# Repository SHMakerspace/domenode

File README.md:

# domenode
A CAN bus controlled, WiFi enabled network of dome node LEDs with many features

# Features
* :heavy_check_mark: ESP32 microcontroller (WiFi, bluetooth)
  * Pads for both ESP32 standalone module and dev board variants
  * OTA wireless firmware updates
* :heavy_check_mark: SN65HVD230 CAN bus transceiver
* :heavy_check_mark: 2x RJ45 connectors for CAN in and passthrough
* :heavy_check_mark: 5x WS2812/NeoPixel for RGB lighting
* :heavy_check_mark: On-board buck regulator
* :heavy_check_mark: 2x push switches
* :heavy_check_mark: Power and GPIO LED
* :heavy_check_mark: many headers for sensors and attachments (I2C, GPIOs, power etc)
* :red_circle: A shield header for expansion boards (to be added)

# Sensors (all optional and do not need to be populated)
Optional features by means of populating those pads are:
* :question: Outer and inner facing LDRs for ambient/transmitted light sensing
* :question: 2x tactile push switches for on-board input
* :question: Heavier duty power RGB LED shield connector (exposes 24V and R,G,B GPIOs)
* :question: IR Tx/Rx and (hopefully!) a ghetto distance sensor
* :question: Speaker
* :question: Capacitive touch
* :question: Microphone - MAX4466 based breakout board connector (footprints could be added to board, alternative idea is I2S)

# Firmware notes
* CAN bus - http://www.barth-dev.de/can-driver-esp32/
* NeoPixels - https://www.instructables.com/id/ESP32-Bluetooth-Ambience-Light-Controller-With-WS2/
* Microphone -https://www.hackster.io/julianfschroeter/esp32-voice-streamer-52bd7e , https://github.com/MrBuddyCasino/ESP32_Alexa
* Speaker - http://www.xtronical.com/basics/audio/dacs-on-esp32/
* IR sensor - https://github.com/mdhiggins/ESP8266-HTTP-IR-Blaster
* I2C bus - https://randomnerdtutorials.com/esp32-with-bmp180-barometric-sensor/

# BoM and Components

## 1. Basic functionality and programming
* 1x ESP32 module
* 1x SOT-223 3v3 LDO regulator
* 2x 0603 10uF ceramic capacitors (decoupling)
* 2x 100uF tantalum capacitors (decoupling)
* 1x 4 pin ISP header
* 1x 2 pin SW0 flashing header
* 2x 0805 LED (power and blink)
* 2x 0603 resistors for LEDs (470 and 1k)
* 1x 0603 10k resistor EN (very much needed, R10)

## 2. NeoPixels
* 9x WS2812 LEDs
* 1x 0603 470 ohm resistor (R13)
* 9x 0603 100nF ceramic capacitors

## 3. External Power
* 1x MINI-360 buck regulator module (U1)
* 1x 1N5819 protection diode
* 1x 1210 10uF >24v capacitor (C1)
* 2x 0603 10uF ceramic capacitors (C2, C4 decoupling)
* 2x RJ45 connectors

## 4. CAN Bus
* 1x SN65HVD230DR transceiver IC (U6)
* 1x 2 pin CANTERM header
* 1x 0603 120 ohm resistor (R16)
* 1x 0603 10k resistor (R17)
* 1x 0603 100nF capacitor (C14, decoupling)

# Serial Programming
Order is:
Black, Green, White, Red 
(GND), (Rx), (Tx), (5V)

#Flashing Procedure
* 1. Determine COM port with command `mode`
* 2. Open terminal in esp32 python environment
* 3. esptool --chip esp32 -p COM<x> write_flash -z 0x1000 <firmware_bin>

Uploading files

ampy -p COM<x> put <file>

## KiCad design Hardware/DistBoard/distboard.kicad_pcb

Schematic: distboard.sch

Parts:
C1: 100uF; CP_EIA-3528-21_Kemet-B_Pad1.50x2.35mm_HandSolder
C2: 10uF; C_0603_1608Metric_Pad1.05x0.95mm_HandSolder
D1: 1N5819; D_DO-41_SOD81_P10.16mm_Horizontal
F1: Fuse; BladeFuse-Mini
J1: POWER_IN; Wago_734-162_1x02_P3.50mm_Horizontal
J2: FAN_HEADER; Molex_KK-6410-02_02x2.54mm_Straight
J4: CAN_1; RJ45_GENERIC
J5: CAN_PI; RJ45_GENERIC
J6: CAN_2; RJ45_GENERIC
J7: CAN_3; RJ45_GENERIC
J8: CAN_4; RJ45_GENERIC
MH1, MH2, MH3, MH4: MountingHole_Pad; MountingHole_3.2mm_M3_Pad_Via
U1: MINI-360
U2, U3, U4: double_usb; USB_A_Wuerth_61400826021_Horizontal_Stacked

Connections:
+5V: C1.1, C2.1, J2.1, U1.4, U2.1, U2.5, U3.1, U3.5, U4.1, U4.5; also elsewhere on the board
CANGND: C1.2, C2.2, J1.2, J2.2, J4.4, J4.5, J4.6, J4.SH, J5.4, J5.5, J5.6, J5.SH, J6.4, J6.5, J6.6, J6.SH, J7.4, J7.5, J7.6, J7.SH, J8.4, J8.5, J8.6, J8.SH, MH1.1, MH2.1, MH3.1, MH4.1, U1.2, U1.3, U2.4, U2.8, U2.9, U3.4, U3.8, U3.9, U4.4, U4.8, U4.9; also elsewhere on the board
CANH: J4.7, J5.7, J6.7, J7.7, J8.7
CANL: J4.8, J5.8, J6.8, J7.8, J8.8
CANV: D1.1 (K), J4.1, J4.2, J4.3, J5.1, J5.2, J5.3, J6.1, J6.2, J6.3, J7.1, J7.2, J7.3, J8.1, J8.2, J8.3, U1.1
unnamed: D1.2 (A), F1.2
unnamed: F1.1, J1.1

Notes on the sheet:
1: VCC 2: VCC 3: VCC 4: GND 5: GND 6: GND 7: CAN+ 8: CAN-

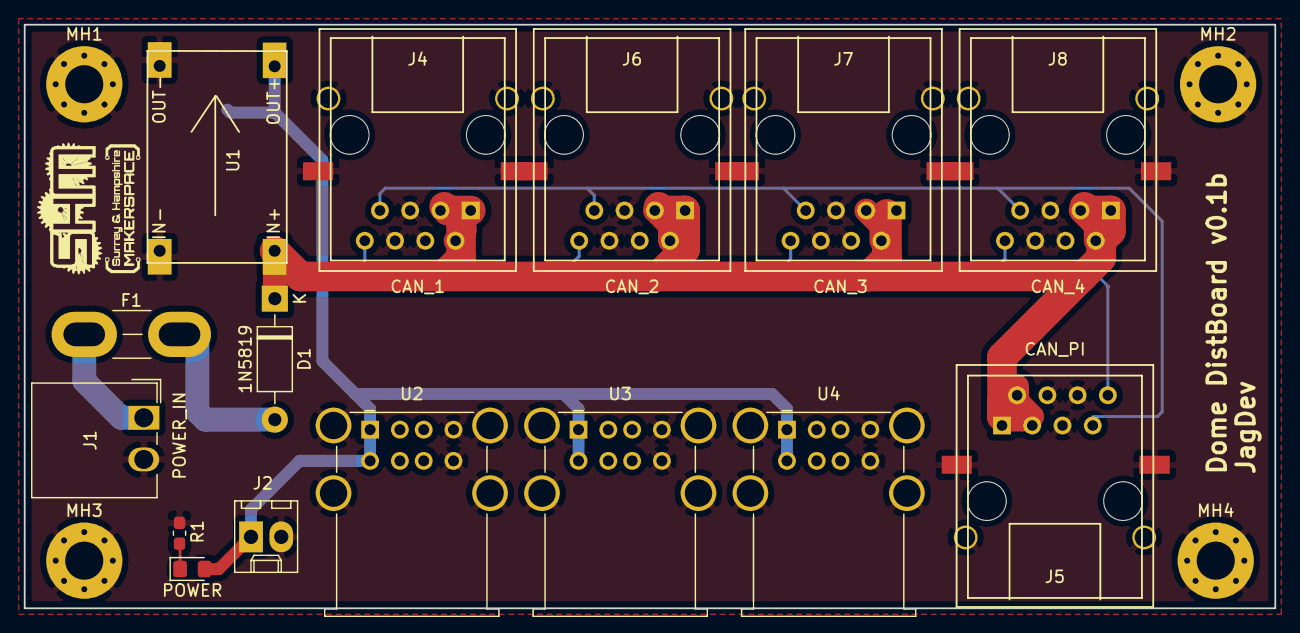
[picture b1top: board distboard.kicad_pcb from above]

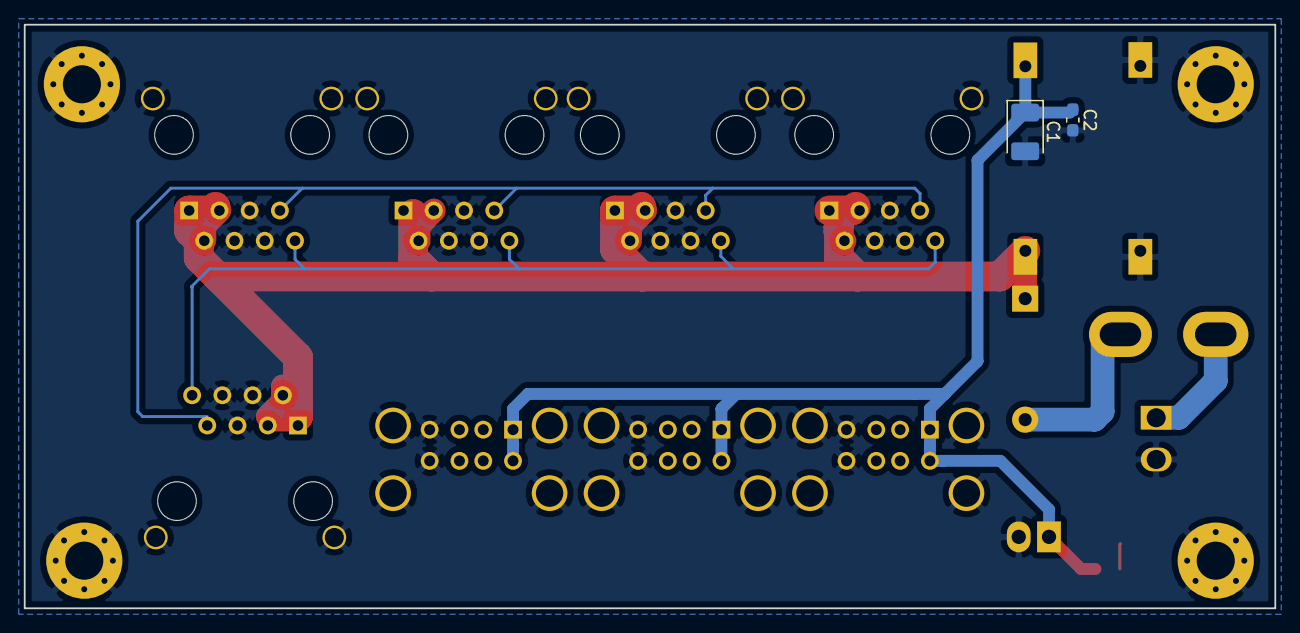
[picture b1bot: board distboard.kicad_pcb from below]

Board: 2 copper layers, 105.0 x 49.0 mm, 22 parts (2 on the bottom side), 8 nets.

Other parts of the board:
D2: POWER; LED_0805_2012Metric_Pad1.15x1.40mm_HandSolder
R1: 1K; R_0603_1608Metric_Pad1.05x0.95mm_HandSolder
shm_logo_small: shm_logo_small

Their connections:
+5V: D2.2; also elsewhere on the board
CANGND: R1.2; also elsewhere on the board
unnamed: D2.1, R1.1

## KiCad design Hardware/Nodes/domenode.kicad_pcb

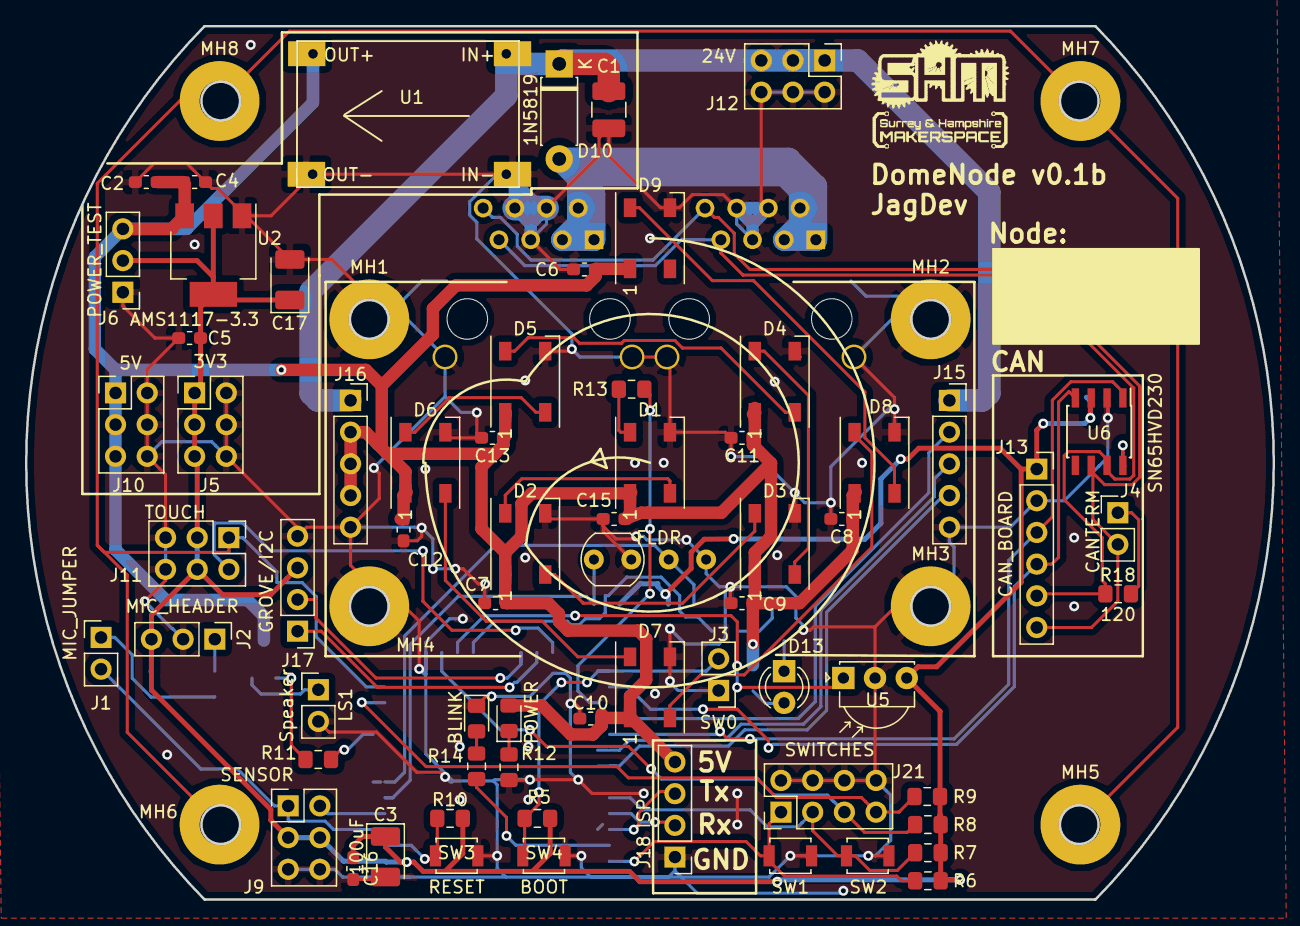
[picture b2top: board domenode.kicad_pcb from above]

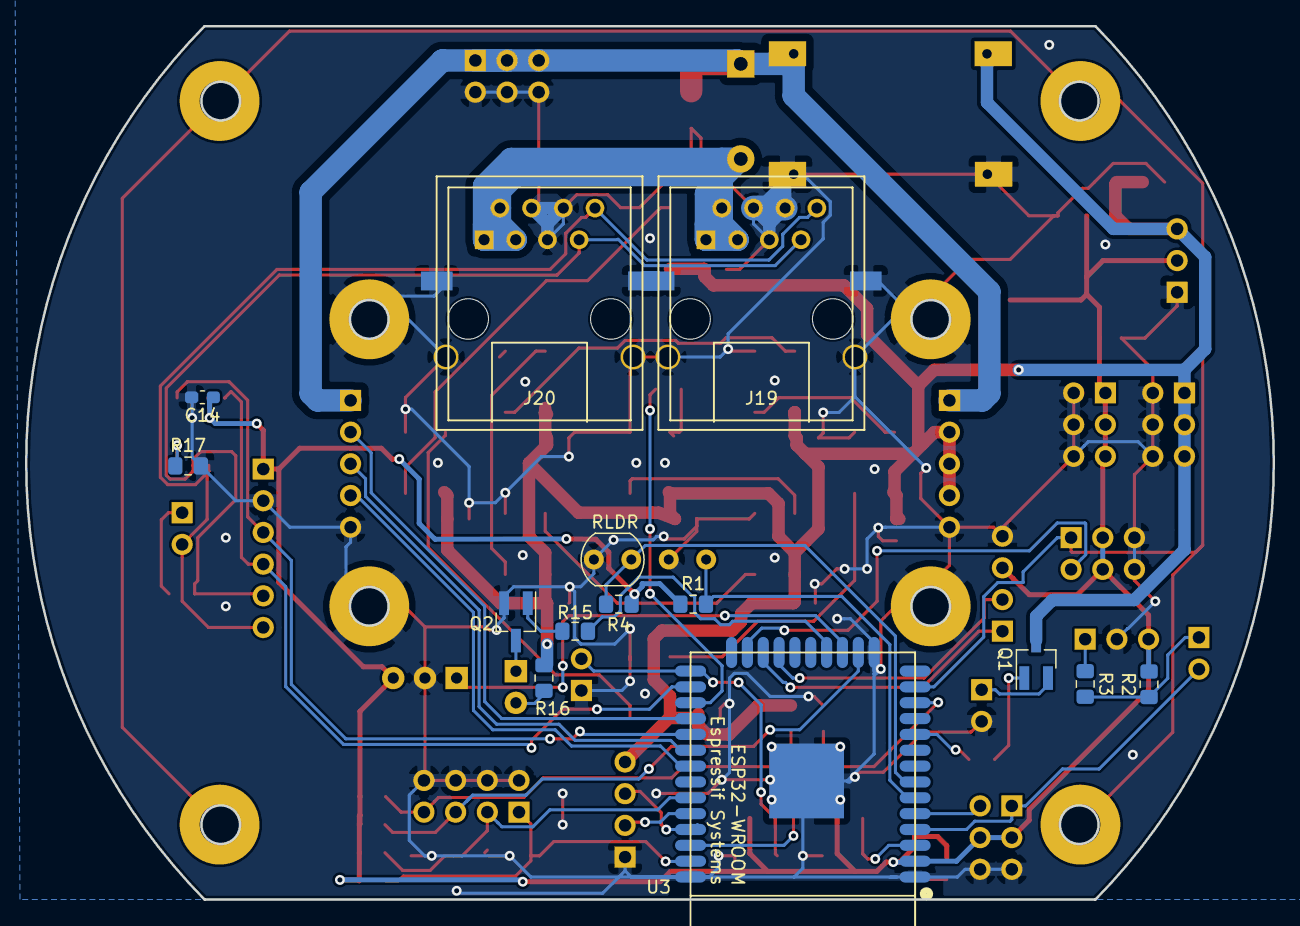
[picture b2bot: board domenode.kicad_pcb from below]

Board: 2 copper layers, 100.0 x 70.0 mm, 89 parts (14 on the bottom side), 53 nets.

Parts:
C1: 10uF; C_1210_3225Metric_Pad1.42x2.65mm_HandSolder
C2, C4, C5, C16: 10uF; C_0603_1608Metric_Pad1.05x0.95mm_HandSolder
C3, C17: 100uF; CP_EIA-3528-21_Kemet-B_Pad1.50x2.35mm_HandSolder
C6, C7, C8, C9, C10, C11, C12, C13, C14, C15: 100nF; C_0603_1608Metric_Pad1.05x0.95mm_HandSolder
D1, D2, D3, D4, D5, D6, D7, D8, D9: WS2812B; LED_WS2812B_PLCC4_5.0x5.0mm_P3.2mm
D10: 1N5819; D_DO-41_SOD81_P7.62mm_Horizontal
D11: POWER; LED_0805_2012Metric_Pad1.15x1.40mm_HandSolder
D12: BLINK; LED_0805_2012Metric_Pad1.15x1.40mm_HandSolder
D13: IRLED; LED_D3.0mm_IRBlack
J1: MIC_JUMPER; PinHeader_1x02_P2.54mm_Vertical
J2: MIC_HEADER; PinHeader_1x03_P2.54mm_Vertical
J3: SW0; PinHeader_1x02_P2.54mm_Vertical
J4: CANTERM; PinHeader_1x02_P2.54mm_Vertical
J5: 3V3; PinHeader_2x03_P2.54mm_Vertical
J6: POWER_TEST; PinHeader_1x03_P2.54mm_Vertical
J9: SENSOR; PinHeader_2x03_P2.54mm_Vertical
J10: 5V; PinHeader_2x03_P2.54mm_Vertical
J11: TOUCH; PinHeader_2x03_P2.54mm_Vertical
J12: 24V; PinHeader_2x03_P2.54mm_Vertical
J13: CAN_BOARD; PinSocket_1x06_P2.54mm_Vertical
J15, J16: RGB_SHIELD; PinSocket_1x05_P2.54mm_Vertical
J17: GROVE/I2C; PinHeader_1x04_P2.54mm_Vertical
J18: ISP; PinHeader_1x04_P2.54mm_Vertical
J19: CAN_IN; RJ45_GENERIC
J20: CAN_OUT; RJ45_GENERIC
J21: SWITCHES; PinHeader_2x04_P2.54mm_Vertical
LDR1: FLDR; Resistor_LDR_5x4.1_RM3
LDR2: RLDR; Resistor_LDR_5x4.1_RM3
LS1: Speaker; PinHeader_1x02_P2.54mm_Vertical
MH1, MH2, MH3, MH4: GND; MountingHole_3.2mm_M3_Pad
MH5, MH6, MH7, MH8: TOUCH5; MountingHole_3.2mm_M3_Pad
Q1: MMBT918 (2N706 equiv); SOT-23_Handsoldering
Q2: MMBT2222A (2N2222 equiv); SOT-23_Handsoldering
R1, R4: 100k; R_0805_2012Metric_Pad1.15x1.40mm_HandSolder
R2: 4K; R_0805_2012Metric_Pad1.15x1.40mm_HandSolder
R3: 5K; R_0805_2012Metric_Pad1.15x1.40mm_HandSolder
R5, R6, R7, R8, R9, R10: 10k; R_0805_2012Metric_Pad1.15x1.40mm_HandSolder
R11, R16: 100; R_0805_2012Metric_Pad1.15x1.40mm_HandSolder
R12, R15: 1K; R_0805_2012Metric_Pad1.15x1.40mm_HandSolder
R13, R14: 470; R_0805_2012Metric_Pad1.15x1.40mm_HandSolder
R17: 10K; R_0805_2012Metric_Pad1.15x1.40mm_HandSolder
R18: 120; R_0805_2012Metric_Pad1.15x1.40mm_HandSolder
SW1: SW1; SW_SPST_B3U-1000P
SW2: SW2; SW_SPST_B3U-1000P
SW3: RESET; SW_SPST_B3U-1000P
SW4: BOOT; SW_SPST_B3U-1000P
U1: MINI-360
U2: AMS1117-3.3; SOT-223-3_TabPin2
U3: ESP32-WROOM
U5: TSDP341xx; Vishay_MOLD-3Pin
U6: SN65HVD230; SOIC-8_3.9x4.9mm_P1.27mm
shm_logo_small: shm_logo_small

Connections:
+5V: C2.1, C4.1, C6.1, C7.1, C8.1, C9.1, C10.1, C11.1, C12.1, C13.1, C15.1, D1.1, D2.1, D3.1, D4.1, D5.1, D6.1, D7.1, D8.1, D9.1, D11.2, J6.3, J10.1, J10.3, J10.5, J16.2, J16.3, J16.4, J18.4, Q1.3, R16.1, U1.4, U2.3
+24V: C1.1, D10.1, J12.1, J12.3, J12.5, J15.1, J16.1, U1.1
BLINK: R14.1, U3.36
BLUE: J15.4, U3.31
CANGND: C1.2, C2.2, C3.2, C4.2, C5.2, C6.2, C7.2, C8.2, C9.2, C10.2, C11.2, C12.2, C13.2, C14.2, C15.2, C16.2, C17.2, D1.3, D2.3, D3.3, D4.3, D5.3, D6.3, D7.3, D8.3, D9.3, D12.1, J2.2, J3.1, J5.2, J5.4, J5.6, J6.1, J9.5, J9.6, J10.2, J10.4, J10.6, J11.5, J11.6, J12.2, J12.4, J12.6, J13.2, J15.5, J16.5, J17.4, J18.1, J19.4, J19.5, J19.6, J19.SH, J20.4, J20.5, J20.6, J20.SH, J21.2, J21.4, J21.6, J21.8, LDR1.2, LDR2.2, LS1.2, MH1.1, MH2.1, MH3.1, MH4.1, Q2.2, R12.2, R17.2, SW1.2, SW2.2, SW3.2, SW4.2, U1.2, U1.3, U2.1, U3.1, U3.15, U3.38, U3.39, U5.2, U6.2
CANH: J13.5, J19.7, J20.7, R18.1, U6.7
CANL: J4.2, J13.6, J19.8, J20.8, U6.6
CANV: D10.2, J19.1, J19.2, J19.3, J20.1, J20.2, J20.3
CRX: J13.4, U3.26, U6.4
CTX: J13.3, U3.29, U6.1
EN: R10.2, SW3.1, U3.3
FLDR: LDR1.1, R1.2, U3.6
GREEN: J15.3, U3.30
IR_RX: U3.17, U5.1
IR_TX: R15.1, U3.18
unnamed: D1.2, D2.4
unnamed: D1.4, R13.1
unnamed: D2.2, D3.4
unnamed: D3.2, D4.4
unnamed: D4.2, D5.4
unnamed: D5.2, D6.4
unnamed: D6.2, D7.4
unnamed: D7.2, D8.4
unnamed: D8.2, D9.4
unnamed: D11.1, R12.1
unnamed: D12.2, R14.2
unnamed: D13.1, Q2.3
unnamed: D13.2, R16.2
unnamed: J1.1, R2.1, R3.2
unnamed: J2.1, R3.1
unnamed: J4.1, R18.2
unnamed: LS1.1, Q1.2
unnamed: Q1.1, R11.1
unnamed: Q2.1, R15.2
unnamed: R17.1, U6.8
PIXELS: R13.2, U3.27
RED: J15.2, U3.28
RLDR: LDR2.1, R4.2, U3.7
RX: J18.2, U3.34
SCL: J17.1, U3.22
SDA: J17.2, U3.21
SPEAKER: R11.2, U3.10
SW0: J3.2, R5.2, SW4.1, U3.25
SW1: J21.1, R6.2, SW1.1, U3.37
SW2: J21.3, R7.2, SW2.1, U3.33
SW3: J21.5, R8.2, U3.16
SW4: J21.7, R9.2, U3.12
TOUCH3: J11.2, U3.23
TOUCH5: J11.1, MH5.1, MH6.1, MH7.1, MH8.1, U3.13
TX: J18.3, U3.35
VCC: C3.1, C5.1, C14.1, C16.1, C17.1, J2.3, J5.1, J5.3, J5.5, J6.2, J9.3, J9.4, J11.3, J11.4, J13.1, J17.3, R1.1, R2.2, R4.1, R5.1, R6.1, R7.1, R8.1, R9.1, R10.1, U2.2, U3.2, U5.3, U6.3
VN: J9.2, U3.5
VP: J1.2, J9.1, U3.4

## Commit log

2018-07-27 Added LPC11C22 library an initial schematic
2018-07-28 Moving to ESP32 and CAN transceiver idea
2018-07-28 Added SN65HVD230 CAN transceiver library (no pin assignments yet).
2018-07-28 Adding LED stuff. Also upgrading to KiCad 5.0
2018-07-28 Upgraded to KiCad 5.0 and did symbol update. Added 5 Neopixels.
2018-07-28 Need decoupling caps on pixels
2018-07-28 Added RGB 'shield' header for a more powerful RGB led. PIxels still need caps :)
2018-07-29 Pixels have caps. Added external connectors.
2018-07-29 Added DevBoard footprint
2018-07-29 Um, tons of changes. Added:
    - Dev board footprint
    - Power regulators and selectors
    - Other things.
2018-07-29 Tidied up a bit
2018-07-29 Added PDF schematic
2018-07-29 More tinkering. Added required on board switches and moved some pins around.
2018-07-29 Added pullups
2018-07-29 Added IR Tx/Rx
2018-07-29 Fixed some pin assignments
2018-07-29 Added simple transistor-powered speaker circuit
2018-07-30 Fixed symbol issues. Need to add kicad .lib files to Git repo
2018-07-30 More connectors, editing.
2018-07-30 Updated board with new buck regulator
2018-07-30 Fixed a couple of mistakes
2018-07-30 Simple tidying
2018-07-30 Fixed CAN bus transceiver circuit. Tidied.
2018-07-30 Organising
2018-07-30 Added simple schematic for distribution board
2018-07-30 Playing with dist board PCB
2018-07-30 Fixed libraries
2018-07-30 Updated PDF
2018-07-31 Added I2C connector
2018-07-31 PDF update
2018-07-31 Removed unnecessary library references
2018-07-31 Organising folders
2018-07-31 Updated documentation
2018-07-31 Added MAX4466 microphone breakout header
2018-07-31 Microphone doc update
2018-07-31 Schematic prettying
2018-07-31 Added capacitive touch ring mounting pads
2018-07-31 Added ground mount points (for shield or whatever)
2018-07-31 Started assigning footprints and started PCB
2018-08-01 More footprint assigns. More PCB design.
2018-08-01 Bit more layout :)
2018-08-01 Populated board and footprints.
2018-08-01 Removed dev board footprint and associated components. No space!
2018-08-01 Added CAN termination header
2018-08-01 Researched C3 - needs to be tantalum, recommended Pad B size.
2018-08-02 Added SHM label somewhere on the PCB
2018-08-02 Shrunk power connectors
2018-08-02 Moved pins around for ESP32 compatibility
2018-08-02 Made board 5mm bigger, Moved ESP32 to back of board
2018-08-02 Added generic RJ45 connector footprint.
2018-08-02 Added 3D RJ45 model
2018-08-02 Added cap for D9
2018-08-02 Sorting power stage
2018-08-02 More wiring and layout
2018-08-02 Changed pins for RLDR and FLDR to ADC1. ADC2 not implemented
2018-08-02 Playing with software
2018-08-03 moved some stuff around and it's looking potentially better
2018-08-03 More PCB work. Added footprint for IR transistor (MMBT2222A)
2018-08-03 wired up CAN L and H
2018-08-03 More PCBing
2018-08-03 Almost done!
2018-08-03 Fixed capacitive pads and traced them out
2018-08-03 woooo
2018-08-03 Added moar decoupling caps and laid out in PCB
2018-08-03 Updated buck regulator footprint to make it easier to solder
2018-08-03 Skookum'd C1
2018-08-03 Changed J16 header to GND. Don't need two sets of power RGB GPIOs
2018-08-05 Added 5v rail to rgb header
2018-08-05 First clean DRC done.
2018-08-05 Added ground vias for bald patches. Second clean DRC
2018-08-05 added LDR models
2018-08-05 Silkscreen tweaks
2018-08-06 New PDF schematic
2018-08-06 Added PCB plots
2018-08-06 Changed pin 1 to 'power input' for DRC check
2018-08-06 Undone neopixel mess up
2018-08-06 Fixing DRC checks in schematic
2018-08-06 Added power flag to fix DRC errors for CANV input
2018-08-06 Redid neopixel wiring
2018-08-06 More wiring. Passes DRC
2018-08-06 Added more grounding vias
2018-08-06 Updated schematic PDF
2018-08-06 board tweaks
2018-08-06 Added 'backup' footprint for RJ45 shield
2018-08-06 Fixed CANL and CANH traces
2018-08-06 minor tweaks
2018-08-06 more minor changes. Added some 'thermal' vias to underside of neopixels
2018-08-06 Track cleanup. DRC check clean.
2018-08-08 Final DRC. Plotted gerbers, ordered v0.1b boards
2018-08-13 Made footprint pad holes bigger
2018-08-13 Finalised node board v0.1b
2018-08-13 Working on dist board
2018-08-13 Finished distboard design
2018-08-13 Gerbers for v0.1b distboard
2018-08-14 Added component guide
2018-08-23 Initial firmware commit
2018-08-23 Laying foundation for EEPROM writing and reading
2018-08-23 Added debug mode to hold at reboots, more EEPROM code
2018-08-23 Variable and string changes
2018-08-24 Replaced EEPROM storage with non-volatile storage, added a method to set node ID
2018-08-24 Print MAC address at boot
2018-08-25 Tided up code, unmounted NVS after read/writing
2018-08-25 Created spreadsheet for planning node IDs and function codes
2018-08-25 Embedded fonts in spreadsheet
2018-08-25 Compressed images
2018-08-26 Added touch capability and started on CAN messages
2018-08-27 Added heartbeat LED, Arduino OTA, tidied up code a little
2018-08-27 Added wifi credential warning
2018-08-27 Added Neopixel support
2018-08-27 Ready to flash!
2018-08-28 Made tweaks to firmware and added dependencies as submodules
2018-08-28 Fixed Submodules
2018-08-28 Init submodules
2018-08-28 Updated readme and added brightness control
2018-08-28 Fixed typo in readme
2018-08-28 Added rainbow mode, refactored code
2018-08-28 Fixed compile issues
2018-08-28 Final firmware before EMF
2018-09-01 Changed boot behaviour to flash neopixel 1 red until wireless is connected
2018-09-01 Add OTA update indicator (yellow)
2018-09-01 some more changes to indication leds
2018-10-16 Committing changes made at EMF
2020-06-04 previous arduino-based work
2020-06-04 Micropython beginnings
2020-06-04 Misc changes
2020-06-04 Adding gitignore
2020-06-04 Some work.
2020-06-06 A few more additions
